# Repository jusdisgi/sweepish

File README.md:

# sweepish
Basically a Ferris Sweep with a Seeed XIAO nrf52840 and Choc switches. My first ever attempt at PCB design.

I watched Joe Scotto's YouTube video on KiCad and figured I would try to replicate my own keyboard (a Sweep Bling LP from Keebmaker) without looking at any existing board designs. Well, except the 3x3 macropad in the video of course.
I also wanted to use the XIAO BLE because I just ordered some.
I feel like it came out pretty well for a first attempt. I hope to have some more knowledgeable people take a look and tell me how I can do better.

Now updated on day 2...learned that a)the battery connects underneath the XIAO, which my design did not allow for, and b)the footprints from Seeed's librery are junk and don't even have those pins. So I got a better footprint from https://github.com/ebastler/marbastlib and added that, a JST connector for the battery, a power switch and a reset button. 

All of that is in the sweepish_v2 directory. Have a look!

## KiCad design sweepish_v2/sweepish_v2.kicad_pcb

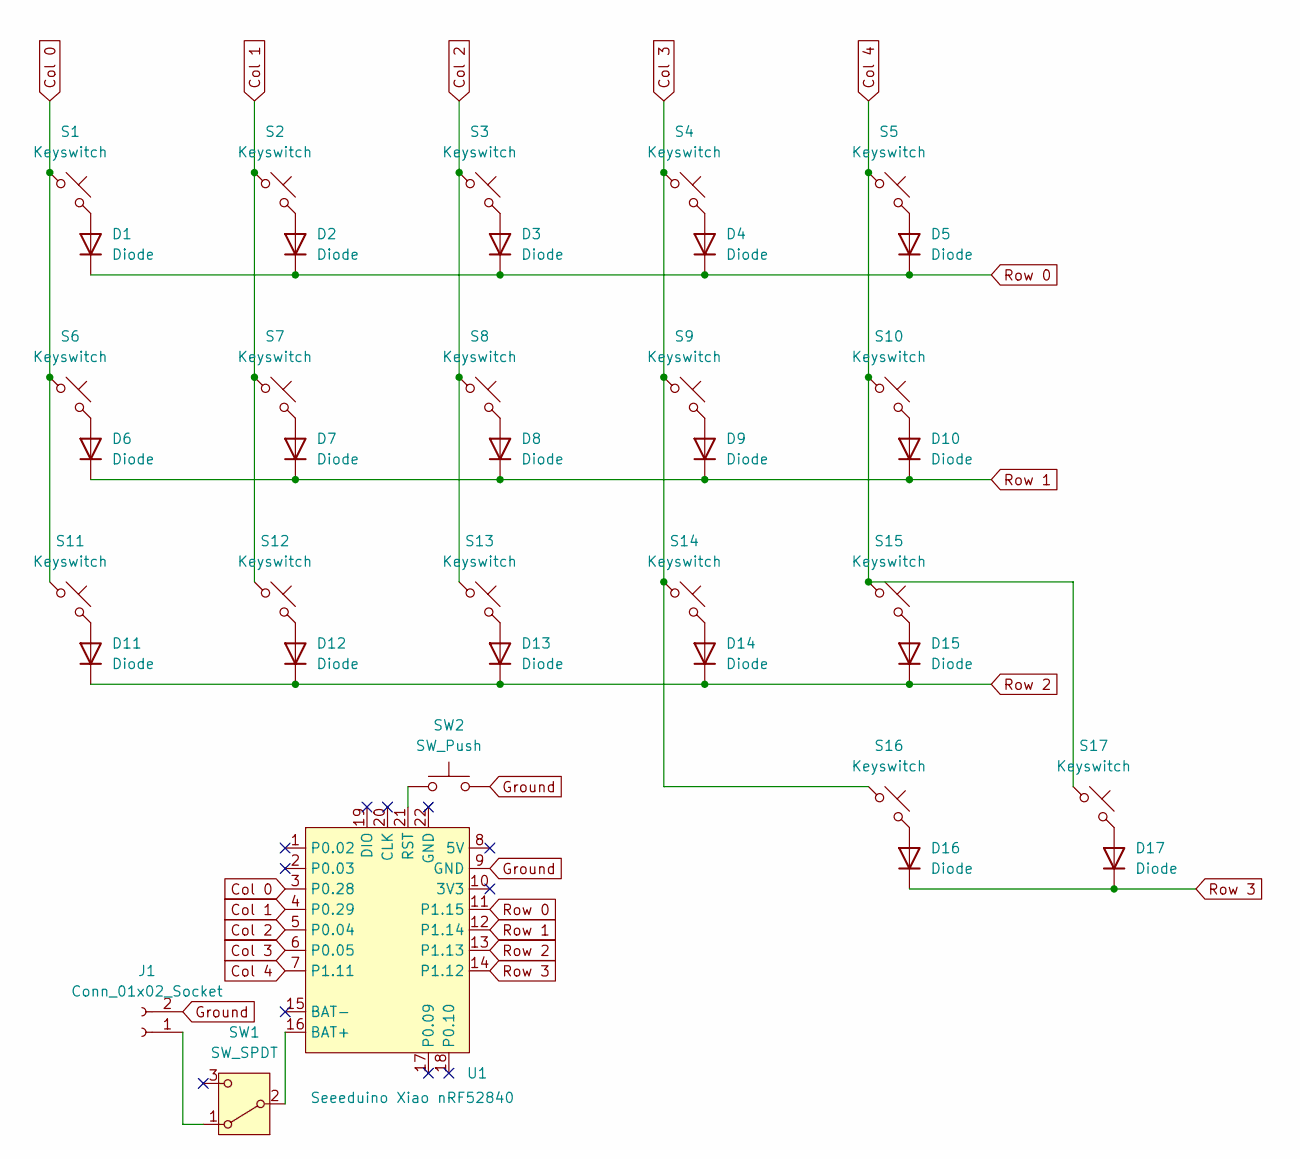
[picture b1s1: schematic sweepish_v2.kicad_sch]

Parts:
D1, D2, D3, D4, D5, D6, D7, D8, D9, D10, D11, D12, D13, D14, D15, D16, D17: Diode; Diode_SOD-123
J1: Conn_01x02_Socket; JST_PH_S2B-PH-SM4-TB_1x02-1MP_P2.00mm_Horizontal
S1, S2, S3, S4, S5, S6, S7, S8, S9, S10, S11, S12, S13, S14, S15, S16, S17: Keyswitch; Choc_V1_1.00u
SW1: SW_SPDT; SW_MSK12C02-HB
SW2: SW_Push; SW_T1A2QR
U1: Seeeduino Xiao nRF52840; Xiao_nRF52840_AC_Reflow

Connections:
Col 0: S1.1, S6.1, S11.1, U1.3 (P0.28)
Col 1: S2.1, S7.1, S12.1, U1.4 (P0.29)
Col 2: S3.1, S8.1, S13.1, U1.5 (P0.04)
Col 3: S4.1, S9.1, S14.1, S16.1, U1.6 (P0.05)
Col 4: S5.1, S10.1, S15.1, S17.1, U1.7 (P1.11)
Ground: J1.2, SW2.2, U1.9 (GND)
unnamed: D1.2 (A), S1.2
unnamed: D2.2 (A), S2.2
unnamed: D3.2 (A), S3.2
unnamed: D4.2 (A), S4.2
unnamed: D5.2 (A), S5.2
unnamed: D6.2 (A), S6.2
unnamed: D7.2 (A), S7.2
unnamed: D8.2 (A), S8.2
unnamed: D9.2 (A), S9.2
unnamed: D10.2 (A), S10.2
unnamed: D11.2 (A), S11.2
unnamed: D12.2 (A), S12.2
unnamed: D13.2 (A), S13.2
unnamed: D14.2 (A), S14.2
unnamed: D15.2 (A), S15.2
unnamed: D16.2 (A), S16.2
unnamed: D17.2 (A), S17.2
unnamed: J1.1, SW1.1 (A)
unnamed: SW1.2 (B), U1.16 (BAT+)
unnamed: SW2.1, U1.21 (RST)
Row 0: D1.1 (K), D2.1 (K), D3.1 (K), D4.1 (K), D5.1 (K), U1.11 (P1.15)
Row 1: D6.1 (K), D7.1 (K), D8.1 (K), D9.1 (K), D10.1 (K), U1.12 (P1.14)
Row 2: D11.1 (K), D12.1 (K), D13.1 (K), D14.1 (K), D15.1 (K), U1.13 (P1.13)
Row 3: D16.1 (K), D17.1 (K), U1.14 (P1.12)

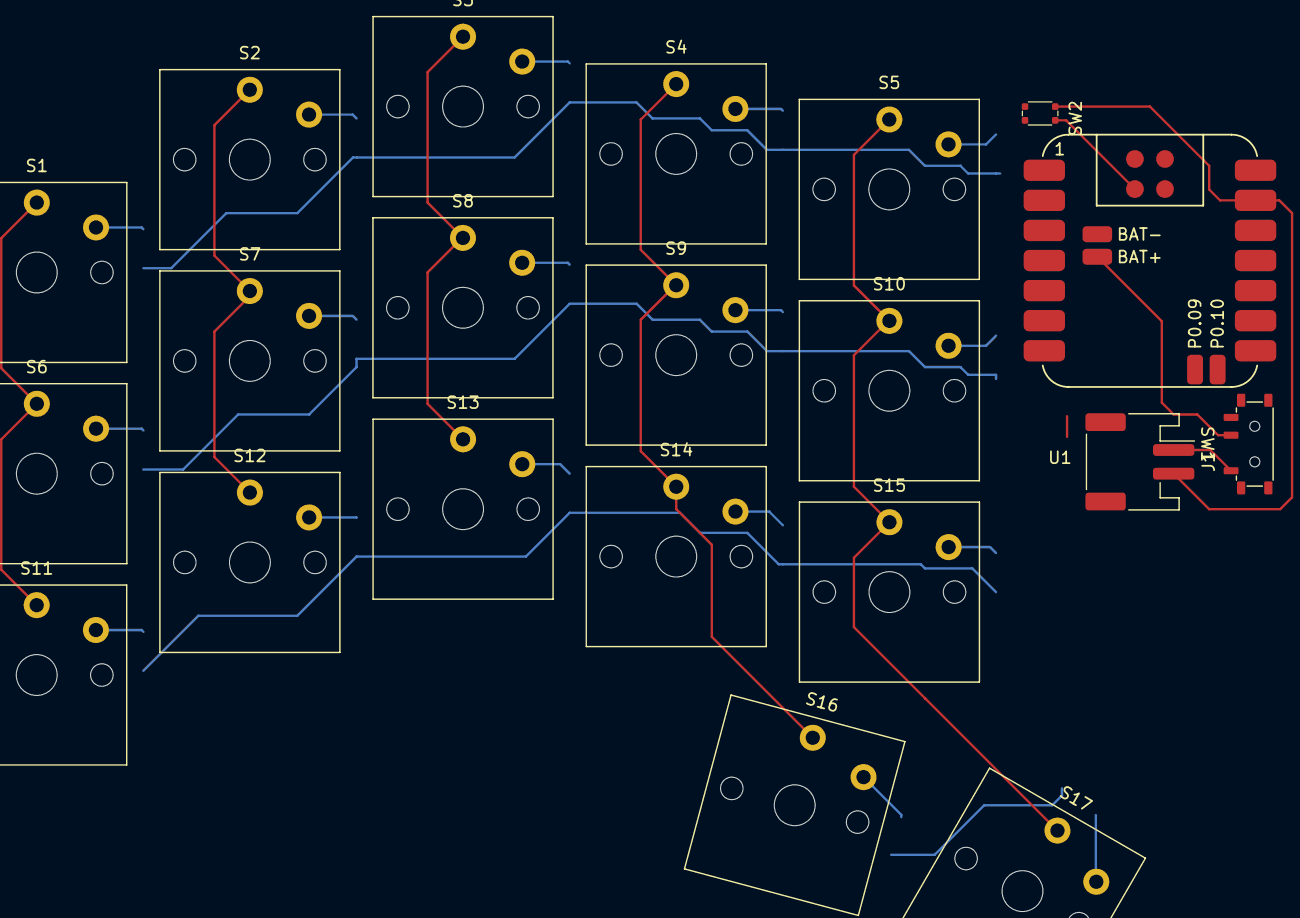
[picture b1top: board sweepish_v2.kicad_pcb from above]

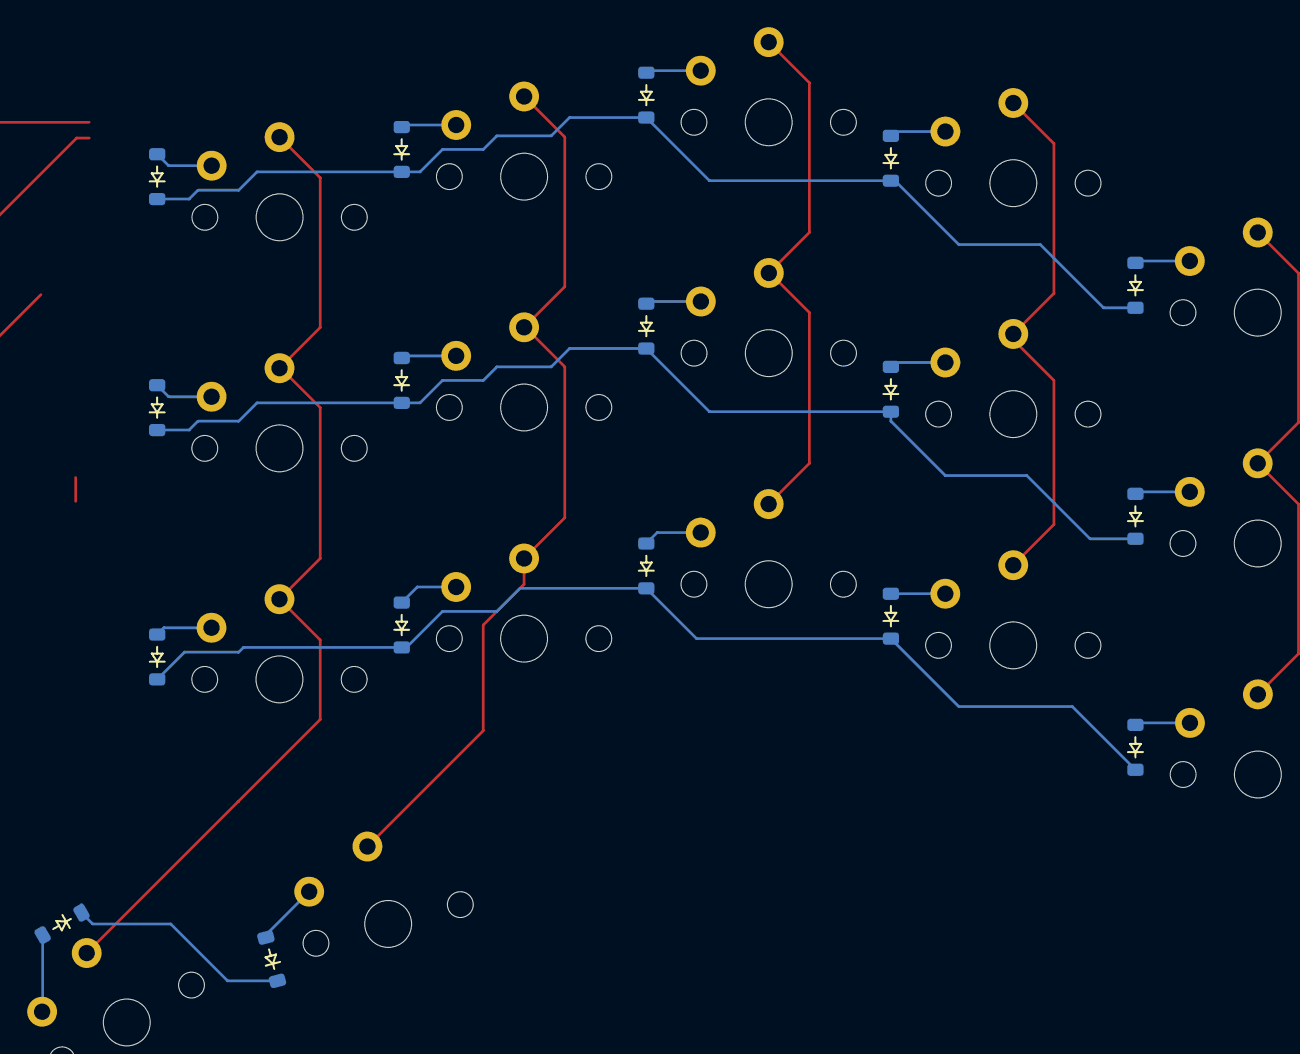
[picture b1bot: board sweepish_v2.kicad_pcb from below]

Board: 2 copper layers, 38 parts (17 on the bottom side), 30 nets.

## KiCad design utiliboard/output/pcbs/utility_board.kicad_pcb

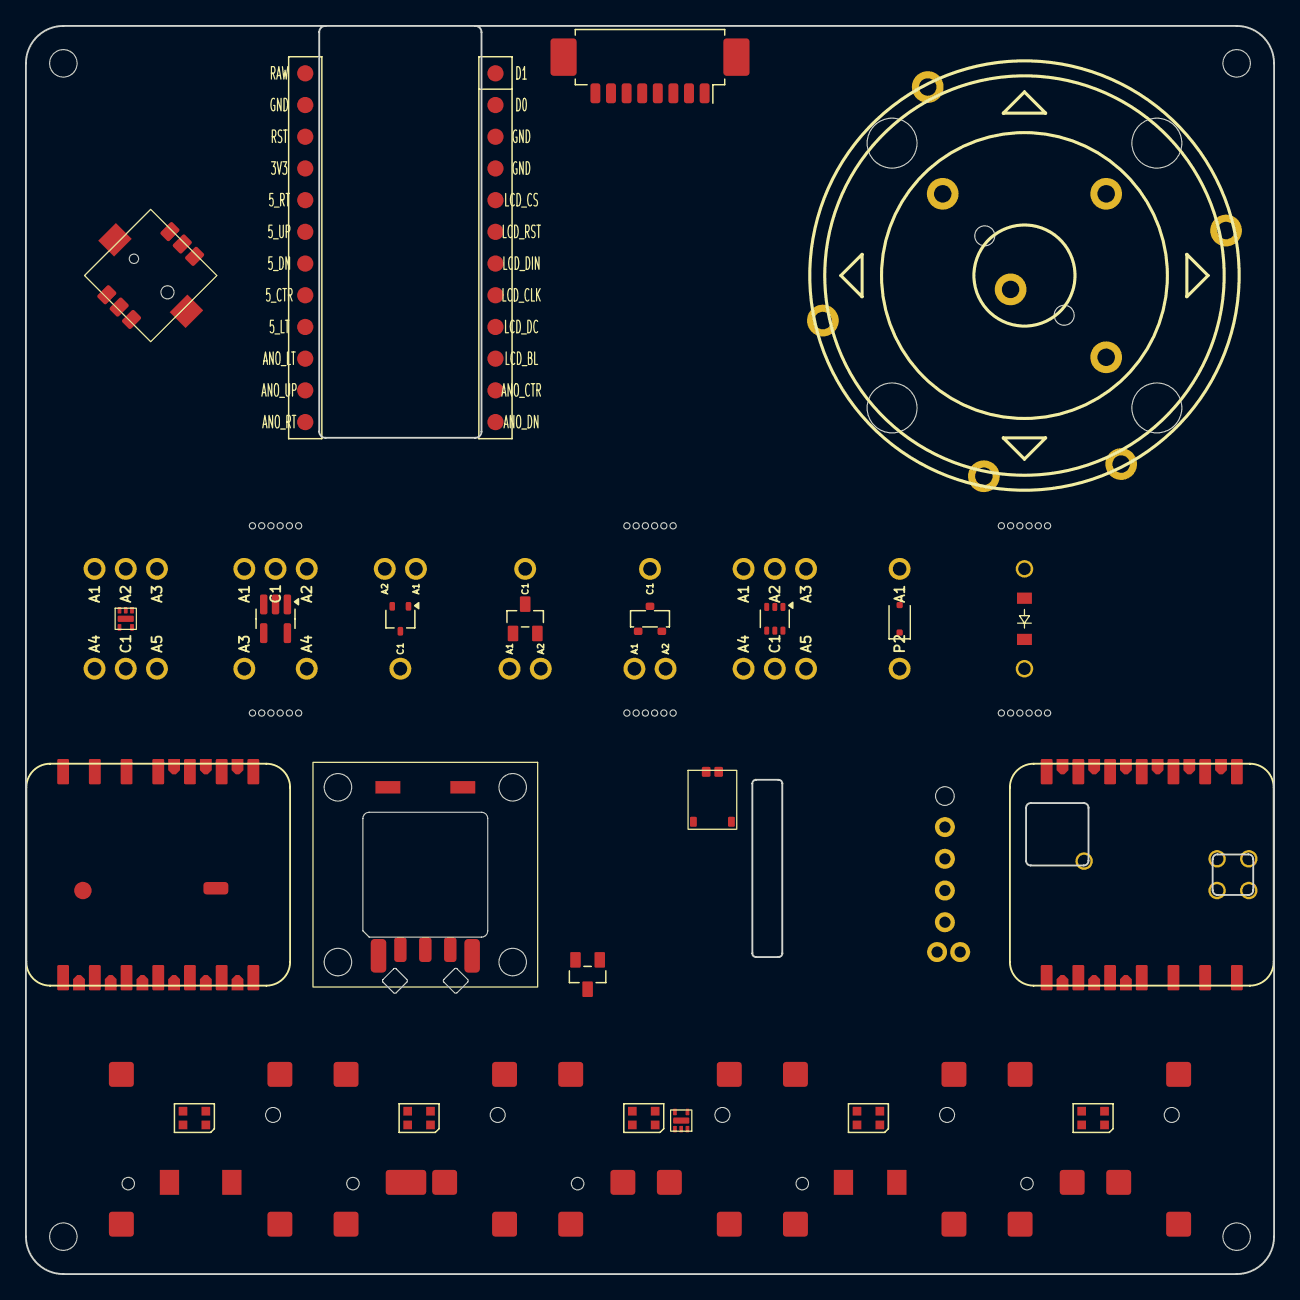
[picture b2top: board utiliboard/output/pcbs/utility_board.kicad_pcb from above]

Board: 2 copper layers, 100.0 x 100.0 mm, 47 parts (0 on the bottom side), 76 nets, no tracks yet.

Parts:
CONN1: Molex_PicoBlade_53261-0871_1x08-1MP_P1.25mm_Horizontal
CONN2: Molex_Pico_EZMate_Plus_1x02
D1, D7: D_MMBD4148PLM
D2, D6: BAV70; BAV70 SOT23
D3: SOT-23
D4: D_SOD-323F
D5: diode_tht_sod123
H1, H2: mounting_hole_plated
LED1, LED2, LED3, LED4, LED5: LED_WS2812B-2020_PLCC4_2.0x2.0mm
MCU1: mcu_nice_nano
MDS1: SKRHADE010_naked
MH1, MH2, MH3, MH4: mounting_hole_npth
RE1: ENCODER_ANO
RE2: CKW12
S2, S3, S4, S5, S6: PG1316S
XX1, XX2, XX3, XX4, XX5, XX6: mousebites 2mm; mousebites_25mm
XX7, XX9, XX11, XX12, XX13, XX15, XX16: 5diode_Breakout_Holes
XX8: SC-74A-5_1.55x2.9mm_P0.95mm
XX10: SOT-323_SC-70
XX14: SOT-363_SC-70-6
XX17, XX18: xiao_plus_smd_prod

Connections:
1A1: D1.1, XX7.1
1A2: D1.2, XX7.2
1A3: D1.3, XX7.3
1A4: D1.4, XX7.4
1A5: D1.5, XX7.6
1C1: D1.6, XX7.5
2A1: XX8.1, XX9.3
2A2: XX8.3, XX9.1
2A3: XX8.4, XX9.4
2A4: XX8.5, XX9.5
2C1: XX8.2, XX9.2
3P1: XX10.1, XX11.1
3P2: XX10.2, XX11.2
3P3: XX10.3, XX11.3
3V3: CONN1.1, MCU1.21, XX17.12, XX18.12
4A1: D2.1, XX12.1
4A2: D2.2, XX12.2
4C1: D2.3, XX12.3
5A1: D3.1, XX13.1
5A2: D3.2, XX13.2
5C1: D3.3, XX13.3
5V: LED1.4, LED2.4, LED3.4, LED4.4, LED5.4, XX17.14, XX18.14
5_CTR: MCU1.17, MDS1.2
5_DN: MCU1.18, MDS1.3
5_LT: MCU1.16, MDS1.1
5_RT: MCU1.20, MDS1.6
5_UP: MCU1.19, MDS1.4
6P1: XX14.1, XX15.3
6P2: XX14.2, XX15.2
6P3: XX14.3, XX15.1
6P4: XX14.4, XX15.4
6P5: XX14.5, XX15.5
6P6: XX14.6, XX15.6
7P1: D4.2, XX16.1
7P2: D4.1, XX16.2
ANO_B: RE1.A, RE1.B
ANO_CTR: MCU1.11, RE1.S1
ANO_DN: MCU1.12, RE1.S2
ANO_LT: MCU1.15, RE1.S5
ANO_RT: MCU1.13, RE1.S3
ANO_UP: MCU1.14, RE1.S4
C0: RE2.S1, S2.1, XX17.19, XX18.19
C1: S3.1, XX17.6, XX18.6
C2: S4.1, XX17.21, XX18.21
C3: S5.1, XX17.9, XX18.9
C4: S6.1, XX17.22, XX18.22
GND: CONN1.2, CONN2.1, LED1.2, LED2.2, LED3.2, LED4.2, LED5.2, MCU1.3, MCU1.4, MCU1.23, MDS1.5, RE1.COM_A, RE1.COM_B, RE2.B, S3.3, S4.3, S5.3, S6.3, XX17.13, XX18.13, XX18.27
LCD_BL: CONN1.8, MCU1.10
LCD_CLK: CONN1.4, MCU1.8
LCD_CS: CONN1.5, MCU1.5
LCD_DC: CONN1.6, MCU1.9
LCD_DIN: CONN1.3, MCU1.7
LCD_RST: CONN1.7, MCU1.6
P0.02: XX17.1, XX18.1
P0.03: XX17.2, XX18.2
P0.15: XX17.15, XX18.15
P0.19: XX17.16, XX18.16
P0.28: XX17.3, XX18.3
P0.29: XX17.4, XX18.4
P0.31: XX17.20, XX18.20
P1.01: XX17.17, XX18.17
P1.15: XX17.11, XX18.11
R0: D7.6, XX17.7, XX18.7
R1: D6.3, XX17.8, XX18.8
RAW: CONN2.2, MCU1.24, XX17.28, XX18.28
RST: MCU1.22, XX17.26, XX18.26
ckw12_to: D6.1, RE2.S2
ckw_a: XX17.10, XX18.10
ckw_b: XX17.23, XX18.23
index_home: D7.1, S5.2
inner_home: D7.4, S6.2
middle_home: D7.2, S4.2
pinky_home: D7.5, S2.2
ring_home: D7.3, S3.2
scroll_a: XX17.18, XX18.18
scroll_b: XX17.5, XX18.5

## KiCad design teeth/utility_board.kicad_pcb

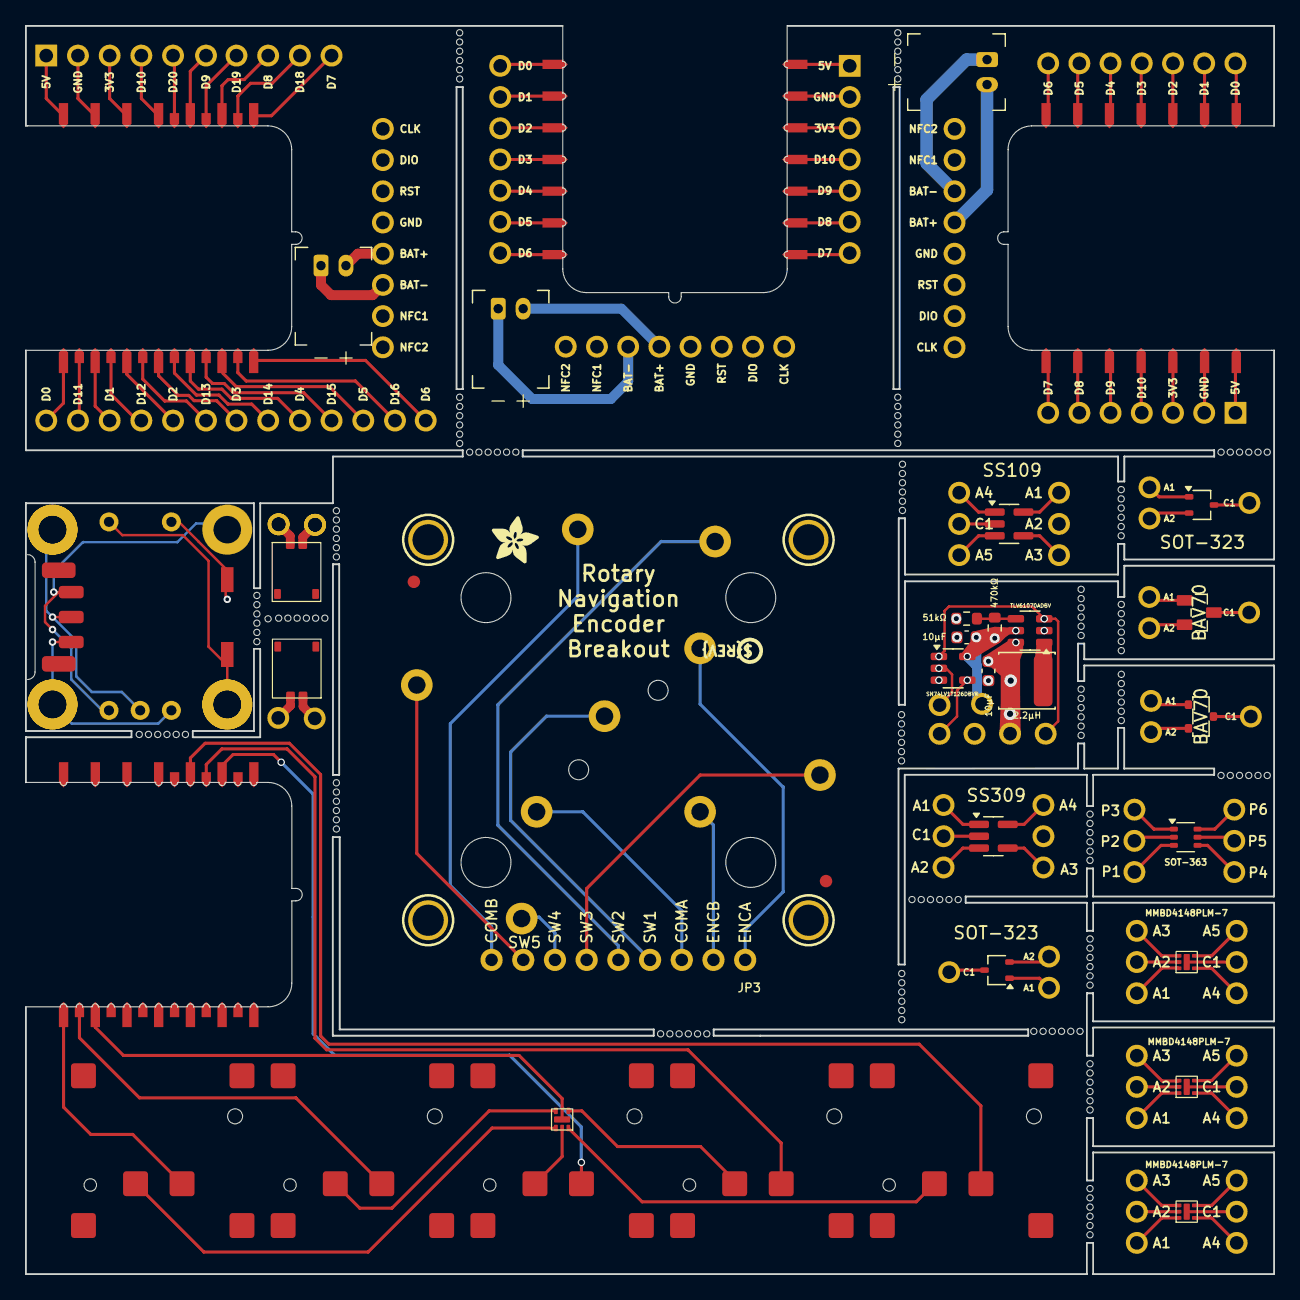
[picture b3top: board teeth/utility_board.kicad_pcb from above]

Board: 2 copper layers, 100.0 x 100.0 mm, 54 parts (1 on the bottom side), 107 nets.

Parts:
C1, C2: 10μF; C_0603_1608Metric
CONN1, CONN1#2: Battery Connector; Molex_Pico_EZMate_Plus_1x02
D1, D2, D3, D8: D_MMBD4148PLM
D5: SOT-23
D6: BAV70; BAV70 SOT23
FID3, FID4: FIDUCIAL_1MM
J1, J2#2, J3, J4#2: xiao_plus_cutout
J1#2, J2, J3#2, J4: Conn_01x01_Pin; my_mount_hole_M2_pad
JP3: 1X09_ROUND_70
JST1, JST1#2, JST1#3: battery_connector_jst_ph_2
L1: 2.2μH; L_CJIANG_FTC404030S_4.1x4.1x3.0_SMD
MCU1, MCU2, MCU3: XIAO_Breakout_Holes
R1: 470kΩ; R_0603_1608Metric
R2: 51kΩ; R_0603_1608Metric
S1, S3, S5, S7, S9: PG1316S_Square_Pads
U1: TLV61070ADBV; SOT-23-6
U2: SN74LV1T126DBVR; SOT-23-5
U$25, U$27, U$29, U$30: MOUNTINGHOLE2.5; MOUNTINGHOLE_2.5_PLATED
U$32: ADAFRUIT_3.5MM
U$33: PCBFEAT-REV-040
X1: ENCODER_ANO
XX17, XX18, XX18#2, XX19, XX19#2, XX19#3, XX21, XX21#2, XX21#3, XX22: 5diode_Breakout_Holes

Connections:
1A1: D1.1, XX17.1
1A2: D1.2, XX17.2
1A3: D1.3, XX17.3
1A4: D1.4, XX17.4
1A5: D1.5, XX17.5
1C1: D1.6, XX17.6
2A1: D2.1, XX18.1
2A2: D2.2, XX18.2
2A3: D2.3, XX18.3
2A4: D2.4, XX18.4
2A5: D2.5, XX18.5
2C1: D2.6, XX18.6
3A1: D3.1, XX19.1
3A2: D3.2, XX19.2
3A3: D3.3, XX19.3
3A4: D3.4, XX19.4
3A5: D3.5, XX19.5
3C1: D3.6, XX19.6
3V3_a: J2#2.12, MCU1.12
3V3_b: J3.12, MCU2.12
3V3_c: J4#2.12, MCU3.12
5A1: D5.1, XX21#3.1
5A2: D5.2, XX21#3.2
5C1: D5.3, XX21#3.3
5V: C2.1, J1.14, R1.1, U1.5 (V_{OUT}), U2.5 (VCC)
5V_EN: U1.3 (EN), U2.1
5V_a: J2#2.14, MCU1.14
5V_b: J3.14, MCU2.14
5V_c: J4#2.14, MCU3.14
6A1: D6.1, XX22.1
6A2: D6.2, XX22.2
6C1: D6.3, XX22.3
BAT-: JST1#2.1, MCU1.29
BAT_a: CONN1.2, CONN1#2.2, JST1#2.2, MCU1.28
BOOST_FB: R1.2, R2.1, U1.4 (V_{FB})
BOOST_SW: L1.2, U1.1 (SW)
COMA: JP3.3, X1.COM_A
COMB: JP3.9, X1.COM_B
D0_a: J2#2.1, MCU1.1
D0_b: J3.1, MCU2.1
D0_c: J4#2.1, MCU3.1
D1_a: J2#2.2, MCU1.2
D1_b: J3.2, MCU2.2
D1_c: J4#2.2, MCU3.2
D2_a: J2#2.3, MCU1.3
D2_b: J3.3, MCU2.3
D2_c: J4#2.3, MCU3.3
D3_a: J2#2.4, MCU1.4
D3_b: J3.4, MCU2.4
D3_c: J4#2.4, MCU3.4
D4_a: J2#2.5, MCU1.5
D4_b: J3.5, MCU2.5
D4_c: J4#2.5, MCU3.5
D5_a: J2#2.6, MCU1.6
D5_b: J3.6, MCU2.6
D5_c: J4#2.6, MCU3.6
D6_a: J2#2.7, MCU1.7
D6_b: J3.7, MCU2.7
D6_c: J4#2.7, MCU3.7
D7_a: J2#2.8, MCU1.8
D7_b: J3.8, MCU2.8
D7_c: J4#2.8, MCU3.8
D8_a: J2#2.9, MCU1.9
D8_b: J3.9, MCU2.9
D8_c: J4#2.9, MCU3.9
D9_a: J2#2.10, MCU1.10
D9_b: J3.10, MCU2.10
D9_c: J4#2.10, MCU3.10
D10_a: J2#2.11, MCU1.11
D10_b: J3.11, MCU2.11
D10_c: J4#2.11, MCU3.11
D11_a: J2#2.15, MCU1.15
D12_a: J2#2.16, MCU1.16
D13_a: J2#2.17, MCU1.17
D14_a: J2#2.18, MCU1.18
D15_a: J2#2.19, MCU1.19
D15_b: JST1#3.2, MCU2.19
D15_c: JST1.2, MCU3.19
D16_a: J2#2.20, MCU1.20
D16_b: JST1#3.1, MCU2.20
D16_c: JST1.1, MCU3.20
D17_a: J2#2.21, MCU1.21
D18_a: J2#2.22, MCU1.22
D19_a: J2#2.23, MCU1.23
ENC_A: JP3.1, X1.A
ENC_B: JP3.2, X1.B
GND: C1.2, C2.2, CONN1.1, CONN1#2.1, J1.13, R2.2, U1.2 (GND), U2.3 (GND), XX19#2.6, XX19#3.2
GND_a: J2#2.13, MCU1.13
GND_b: J3.13, MCU2.13
GND_c: J4#2.13, MCU3.13
P0.02: J1.1, S1.2
P0.03: D8.6, J1.2
P0.15: J1.15, S3.2
P1.05: J1.22, S7.2
P1.13: J1.9, S5.2
P1.14: J1.10, S9.2
RAW: C1.1, L1.1, U1.6 (V_{IN})
SW1: JP3.4, X1.S1
SW2: JP3.5, X1.S2
SW3: JP3.6, X1.S3
SW4: JP3.7, X1.S4
SW5: JP3.8, X1.S5
index_home: D8.4, S7.1
inner_home: D8.1, S9.1
middle_home: D8.2, S5.1
pinky_home: D8.3, S1.1
ring_home: D8.5, S3.1

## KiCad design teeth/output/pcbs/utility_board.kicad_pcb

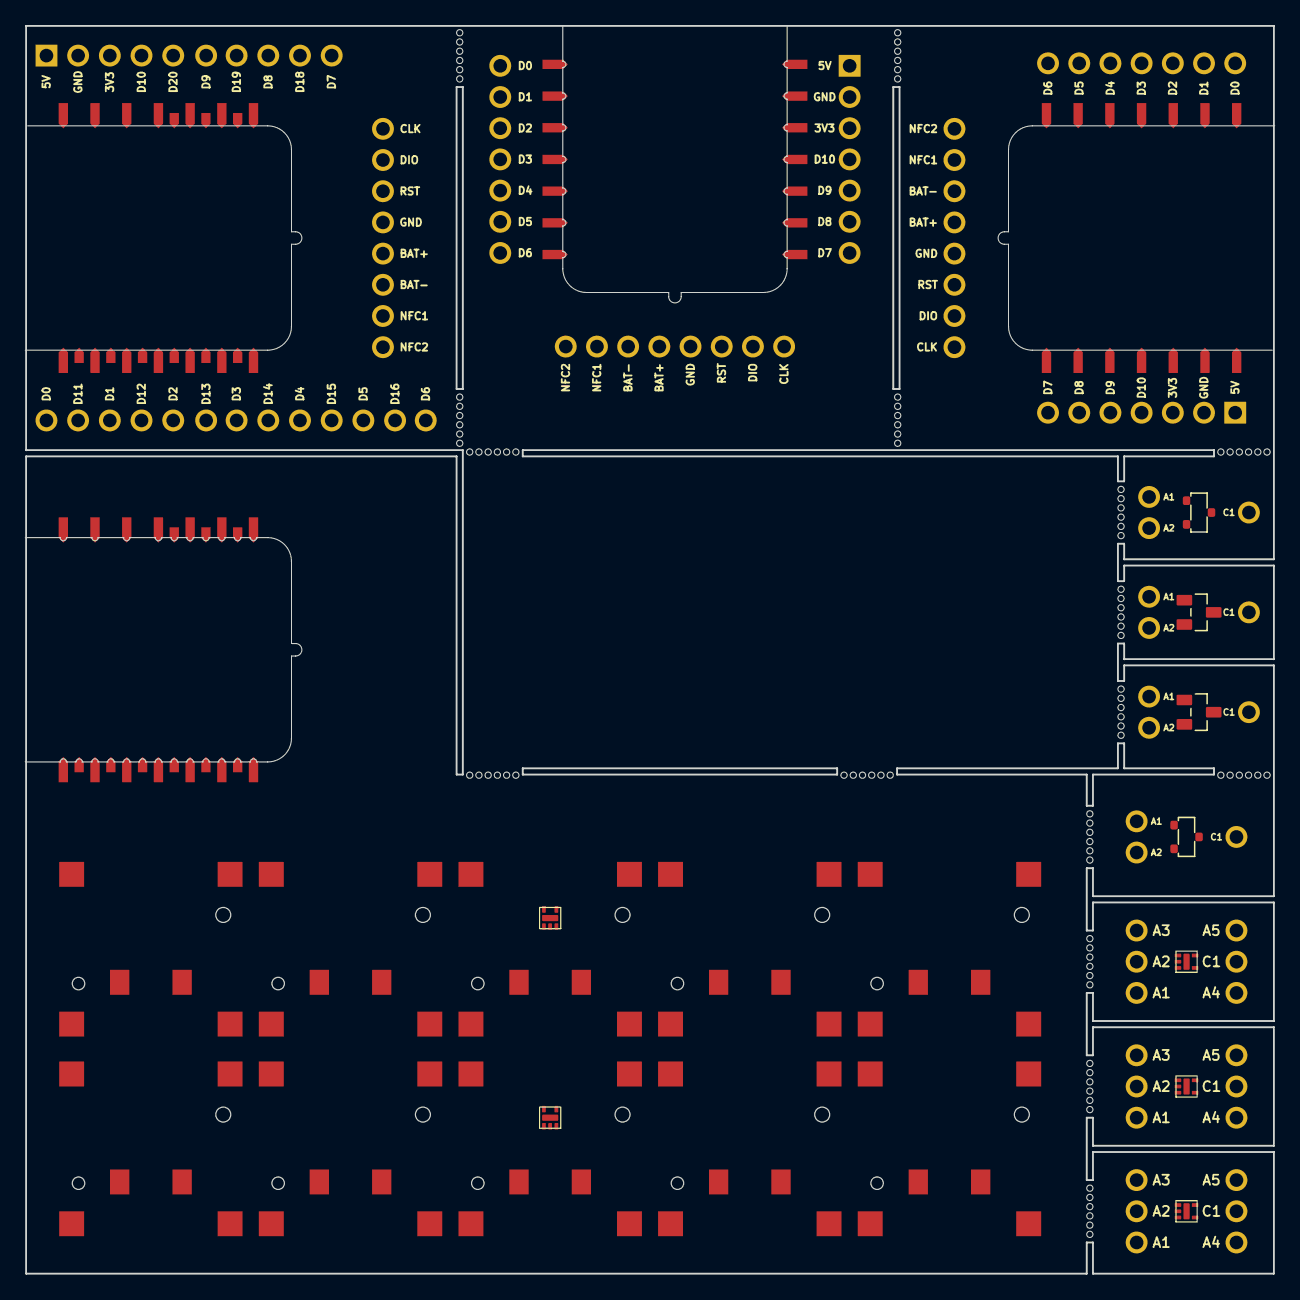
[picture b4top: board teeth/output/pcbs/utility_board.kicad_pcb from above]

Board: 2 copper layers, 100.0 x 100.0 mm, 49 parts (0 on the bottom side), 98 nets, no tracks yet.

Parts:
D1, D2, D3, D8, D9: D_MMBD4148PLM
D4, D6: BAV70; BAV70 SOT23
D5, D7: SOT-23
J1, J2, J3, J4: xiao_plus_cutout
MCU1, MCU2, MCU3: XIAO_Breakout_Holes
S1, S2, S3, S4, S5, S6, S7, S8, S9, S10: CPG1316S01D02_mikeholscher
XX1, XX2, XX3, XX4, XX5, XX6, XX7, XX8, XX9, XX10, XX11, XX12, XX13, XX14, XX15, XX16: mousebites 2mm; mousebites_25mm
XX17, XX18, XX19, XX20, XX21, XX22, XX23: 5diode_Breakout_Holes

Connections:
1A1: D1.1, XX17.1
1A2: D1.2, XX17.2
1A3: D1.3, XX17.3
1A4: D1.4, XX17.4
1A5: D1.5, XX17.5
1C1: D1.6, XX17.6
2A1: D2.1, XX18.1
2A2: D2.2, XX18.2
2A3: D2.3, XX18.3
2A4: D2.4, XX18.4
2A5: D2.5, XX18.5
2C1: D2.6, XX18.6
3A1: D3.1, XX19.1
3A2: D3.2, XX19.2
3A3: D3.3, XX19.3
3A4: D3.4, XX19.4
3A5: D3.5, XX19.5
3C1: D3.6, XX19.6
3V3_a: J2.12, MCU1.12
3V3_b: J3.12, MCU2.12
3V3_c: J4.12, MCU3.12
4A1: D4.1, XX20.1
4A2: D4.2, XX20.2
4C1: D4.3, XX20.3
5A1: D5.1, XX21.1
5A2: D5.2, XX21.2
5C1: D5.3, XX21.3
5V_a: J2.14, MCU1.14
5V_b: J3.14, MCU2.14
5V_c: J4.14, MCU3.14
6A1: D6.1, XX22.1
6A2: D6.2, XX22.2
6C1: D6.3, XX22.3
7A1: D7.1, XX23.1
7A2: D7.2, XX23.2
7C1: D7.3, XX23.3
D0_a: J2.1, MCU1.1
D0_b: J3.1, MCU2.1
D0_c: J4.1, MCU3.1
D1_a: J2.2, MCU1.2
D1_b: J3.2, MCU2.2
D1_c: J4.2, MCU3.2
D2_a: J2.3, MCU1.3
D2_b: J3.3, MCU2.3
D2_c: J4.3, MCU3.3
D3_a: J2.4, MCU1.4
D3_b: J3.4, MCU2.4
D3_c: J4.4, MCU3.4
D4_a: J2.5, MCU1.5
D4_b: J3.5, MCU2.5
D4_c: J4.5, MCU3.5
D5_a: J2.6, MCU1.6
D5_b: J3.6, MCU2.6
D5_c: J4.6, MCU3.6
D6_a: J2.7, MCU1.7
D6_b: J3.7, MCU2.7
D6_c: J4.7, MCU3.7
D7_a: J2.8, MCU1.8
D7_b: J3.8, MCU2.8
D7_c: J4.8, MCU3.8
D8_a: J2.9, MCU1.9
D8_b: J3.9, MCU2.9
D8_c: J4.9, MCU3.9
D9_a: J2.10, MCU1.10
D9_b: J3.10, MCU2.10
D9_c: J4.10, MCU3.10
D10_a: J2.11, MCU1.11
D10_b: J3.11, MCU2.11
D10_c: J4.11, MCU3.11
D11_a: J2.15, MCU1.15
D12_a: J2.16, MCU1.16
D13_a: J2.17, MCU1.17
D14_a: J2.18, MCU1.18
D15_a: J2.19, MCU1.19
D16_a: J2.20, MCU1.20
D17_a: J2.21, MCU1.21
D18_a: J2.22, MCU1.22
D19_a: J2.23, MCU1.23
GND_a: J2.13, MCU1.13
GND_b: J3.13, MCU2.13
GND_c: J4.13, MCU3.13
P0.02: J1.1, S1.2, S2.2
P0.03: D8.6, J1.2
P0.15: J1.15, S3.2, S4.2
P1.03: D9.6, J1.21
P1.05: J1.22, S7.2, S8.2
P1.13: J1.9, S5.2, S6.2
P1.14: J1.10, S9.2, S10.2
index_home: D8.1, S7.1
index_top: D9.1, S8.1
inner_home: D8.4, S9.1
inner_top: D9.4, S10.1
middle_home: D8.2, S5.1
middle_top: D9.2, S6.1
pinky_home: D8.5, S1.1
pinky_top: D9.5, S2.1
ring_home: D8.3, S3.1
ring_top: D9.3, S4.1

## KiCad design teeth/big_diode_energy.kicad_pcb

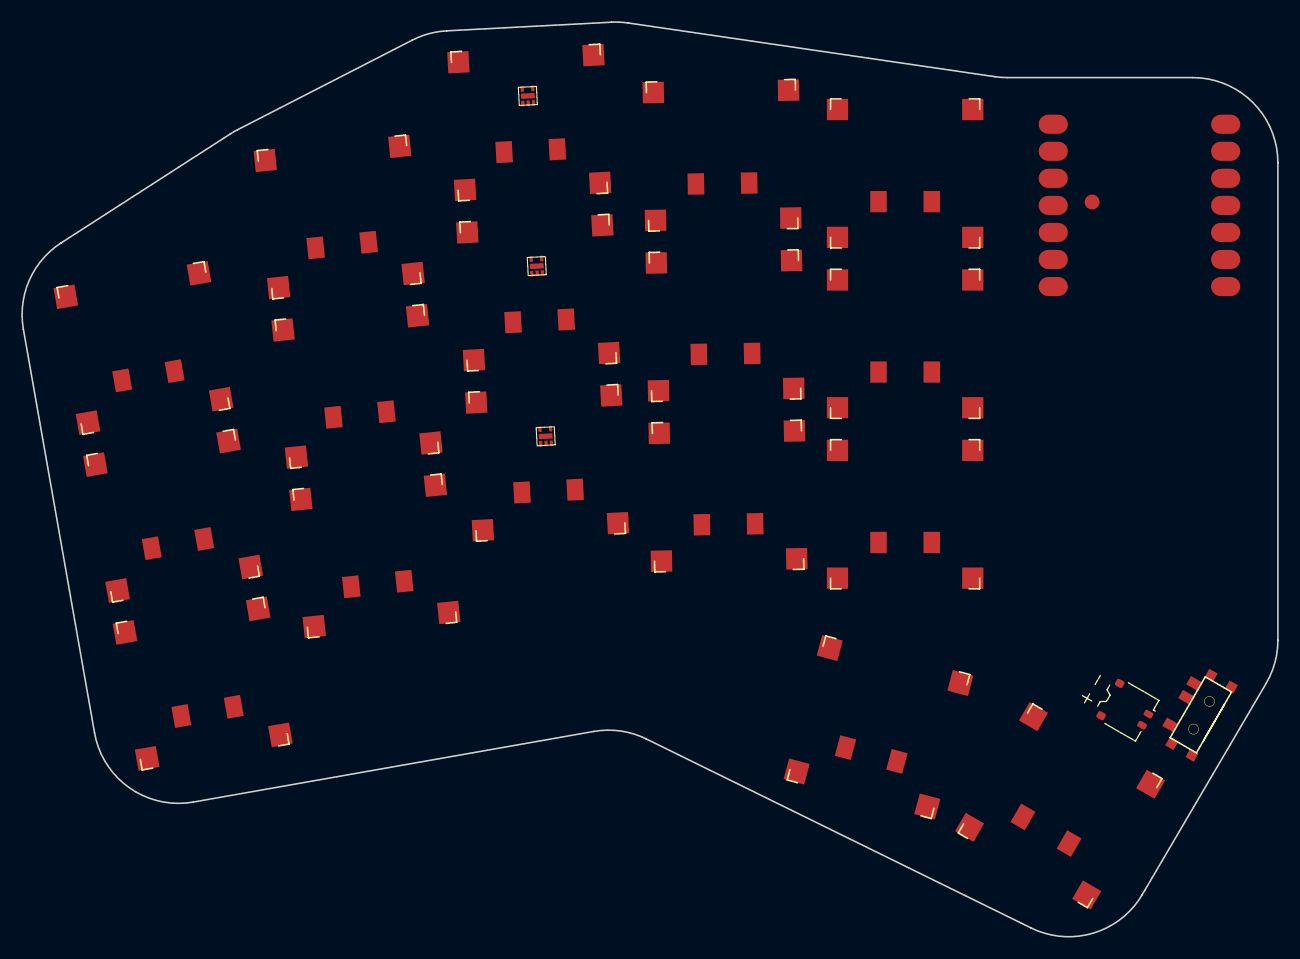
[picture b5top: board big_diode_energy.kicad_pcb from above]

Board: 2 copper layers, 117.9 x 85.9 mm, 23 parts (0 on the bottom side), 26 nets, no tracks yet.

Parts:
CONN1: battery_connector_molex_pico_ezmate_1x02
D1, D2, D3: D_MMBD4148PLM
MCU1: xiao_smd
S1, S2, S3, S4, S5, S6, S7, S8, S9, S10, S11, S12, S13, S14, S15, S16, S17: PG1316S
T1: SPDT_C128955

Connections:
BAT: MCU1.19, T1.2
BAT_P: CONN1.2, T1.1
D0: D3.6, MCU1.1
D1: MCU1.2, S7.2, S8.2, S9.2
D2: D2.6, MCU1.3
D3: MCU1.4, S4.2, S5.2, S6.2
D4: D1.6, MCU1.5
D5: MCU1.6, S1.2, S2.2, S3.2
D8: MCU1.9, S10.2, S11.2, S12.2, S16.2
D10: MCU1.11, S13.2, S14.2, S15.2, S17.2
GND: CONN1.1, MCU1.13
index_bottom: D1.1, S10.1
index_home: D2.1, S11.1
index_top: D3.1, S12.1
inner_bottom: D1.4, S13.1
inner_home: D2.4, S14.1
inner_top: D3.4, S15.1
middle_bottom: D1.2, S7.1
middle_home: D2.2, S8.1
middle_top: D3.2, S9.1
pinky_bottom: D1.5, S1.1
pinky_home: D2.5, S2.1
pinky_top: D3.5, S3.1
ring_bottom: D1.3, S4.1
ring_home: D2.3, S5.1
ring_top: D3.3, S6.1

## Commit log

2025-04-06 Uploaded KiCad project files.
    This was the first PCB I have ever designed...installed KiCad a few hours ago. Not recommended for actual use.
2025-04-06 Uploaded KiCad Files
2025-04-07 Some yaml and pcb files
    My limited attempts at messing around with ergogen.
2025-04-07 New diode footprint
2025-04-18 Add teeth project for testing various stuff
2025-04-18 Add beginnings of utility board ergogen yaml.
2025-04-22 Add xiao cutout footprint to utility board.
2025-04-22 More work on utility board, complex xiao slot complete. Fixed email address.
2025-04-23 Add through-hole array for xiao breakouts, clean up simple cutout, fix nets.
2025-04-25 Add wire holes on xiao slots, work on layout.
2025-04-29 Add more slots/bites to utility board, work on bav70.
2025-04-30 Add BAV70 breakouts and associated slots/bites.
2025-04-30 Fix PG1316S footprint (add stabilizer holes)
2025-06-20 Finish up utility board.
2025-06-30 Create new utility board version with 5-way, CKW12, ANO, an cutout-mount nice nano.
